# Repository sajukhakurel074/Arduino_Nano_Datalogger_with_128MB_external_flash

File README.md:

# DataLogger

This PCB consist of :
- a pressure sensor -> BMP180
- Acclerometer & Gyroscope -> MPU 6050 
- SD Card Module
- Arduino NANO  
- 12V DC power supply
- 2 layer PCB
- 128MB external Flash with spi

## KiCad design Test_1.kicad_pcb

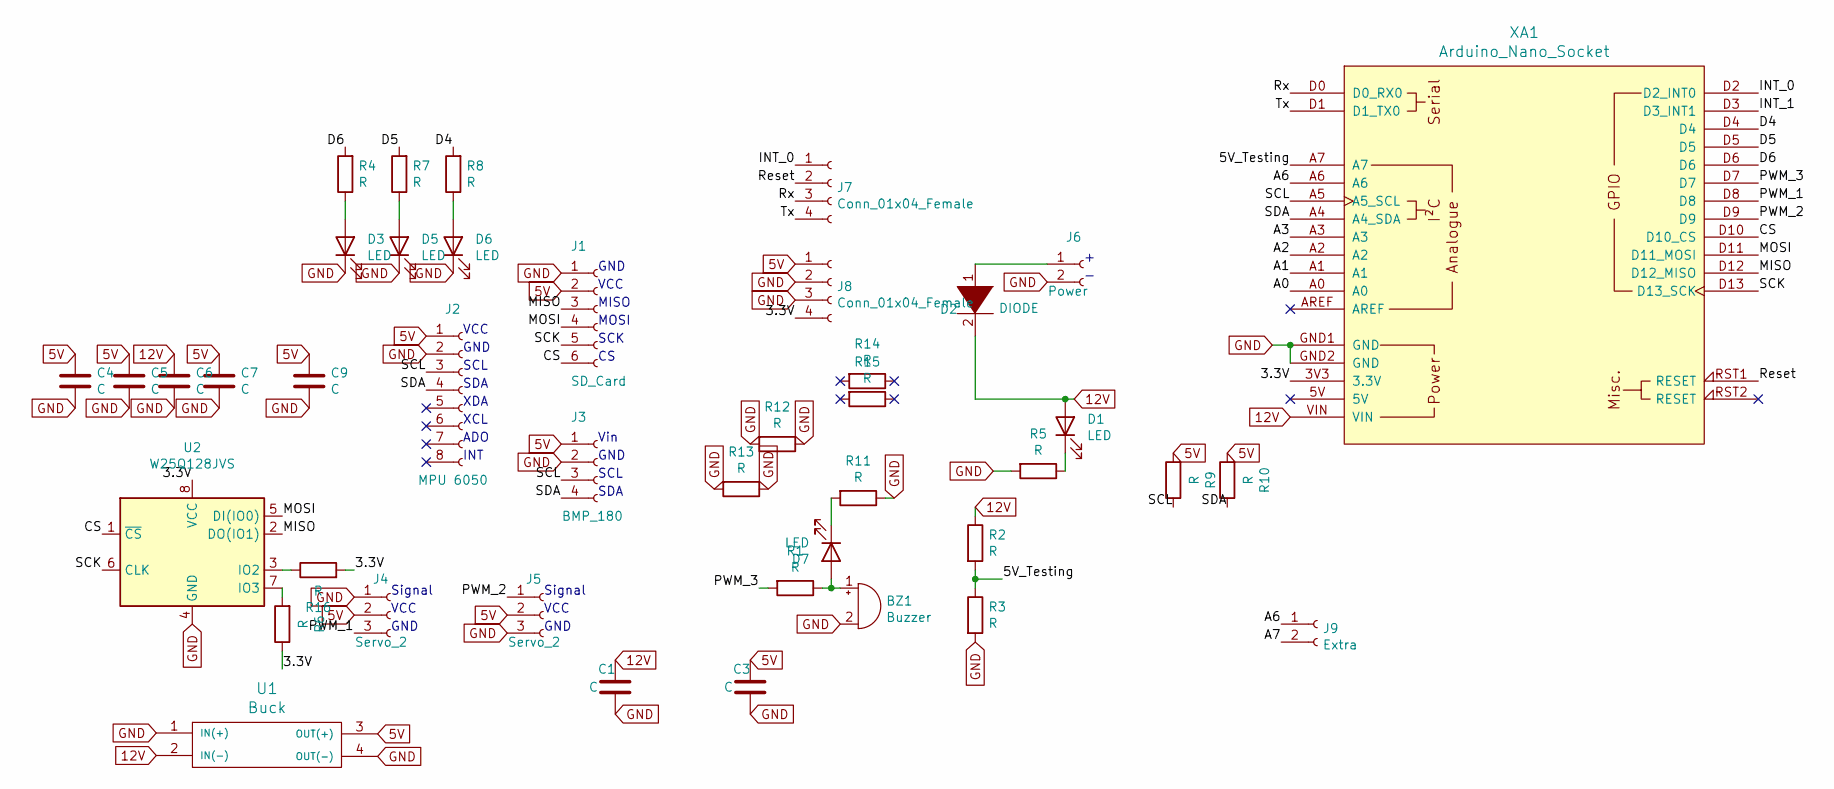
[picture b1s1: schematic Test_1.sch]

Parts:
BZ1: Buzzer; Buzzer_12x9.5RM7.6
C1, C3: C; Capacitor_100uF
C4, C5, C6, C7, C9: C; Capacitor_Disc_Small
D1, D3, D5, D6, D7: LED; LED_D3.0mm
D2: DIODE; Diode_Medium
J1: SD_Card; PinSocket_1x06_P2.54mm_Vertical
J2: MPU 6050; PinSocket_1x08_P2.54mm_Vertical
J3: BMP_180; PinSocket_1x04_P2.54mm_Vertical
J4, J5: Servo_2; Connector_Bornier_3
J6: Power; Solar_Connector
J7, J8: Conn_01x04_Female; PinSocket_1x04_P2.54mm_Vertical
J9: Extra; PinHeader_1x02_P2.54mm_Vertical
R1, R2, R3, R4, R5, R6, R7, R8, R9, R10, R11, R12, R13, R14, R15, R16: R; Resistor_small
U1: Buck; Buck 5A
U2: W25Q128JVS; dip8
XA1: Arduino_Nano_Socket

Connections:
5V: C3.2, C4.1, C5.1, C7.1, C9.1, J1.2, J2.1, J3.1, J4.2, J5.2, J8.1, R9.2, R10.2, U1.3 (OUT(+))
12V: C1.2, C6.1, D1.2 (A), D2.2 (A), R2.1, U1.2 (IN(-)), XA1.VIN
/3.3V: J8.4, R6.1, R16.2, U2.8 (VCC), XA1.3V3 (3.3V)
/5V_Testing: R2.2, R3.1, XA1.A7
/A0: XA1.A0
/A1: XA1.A1
/A2: XA1.A2
/A6: J9.1, XA1.A6
/CS: J1.6, U2.1 (~CS), XA1.D10 (D10_CS)
/D4: R8.2, XA1.D4
/D5: R7.2, XA1.D5
/D6: R4.2, XA1.D6
/INT_0: J7.1, XA1.D2 (D2_INT0)
/INT_1: XA1.D3 (D3_INT1)
/MISO: J1.3, U2.2 (DO(IO1)), XA1.D12 (D12_MISO)
/MOSI: J1.4, U2.5 (DI(IO0)), XA1.D11 (D11_MOSI)
/PWM_1: J4.3, XA1.D8
/PWM_2: J5.1, XA1.D9
/PWM_3: R1.2, XA1.D7
/Reset: J7.2, XA1.RST1 (RESET)
/Rx: J7.3, XA1.D0 (D0_RX0)
/SCK: J1.5, U2.6 (CLK), XA1.D13 (D13_SCK)
/SCL: J2.3, J3.3, R9.1, XA1.A5 (A5_SCL)
/SDA: J2.4, J3.4, R10.1, XA1.A4 (A4_SDA)
/Tx: J7.4, XA1.D1 (D1_TX0)
GND: BZ1.2 (+), C1.1, C3.1, C4.2, C5.2, C6.2, C7.2, C9.2, D3.1 (K), D5.1 (K), D6.1 (K), J1.1, J2.2, J3.2, J4.1, J5.3, J6.2, J8.2, J8.3, R3.2, R5.2, R11.1, R12.1, R12.2, R13.1, R13.2, U1.1 (IN(+)), U1.4 (OUT(-)), U2.4 (GND), XA1.GND1 (GND), XA1.GND2 (GND); also elsewhere on the board
unnamed: BZ1.1 (-), D7.2 (A), R1.1
unnamed: D1.1 (K), R5.1
unnamed: D2.1 (K), J6.1
unnamed: D3.2 (A), R4.1
unnamed: D5.2 (A), R7.1
unnamed: D6.2 (A), R8.1
unnamed: D7.1 (K), R11.2
unnamed: R6.2, U2.7 (IO3)
unnamed: R16.1, U2.3 (IO2)

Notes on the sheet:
GND
VCC
MISO
MOSI
SCK
Signal
VCC
GND
SCL
SDA
XDA
XCL
ADO
INT
Vin

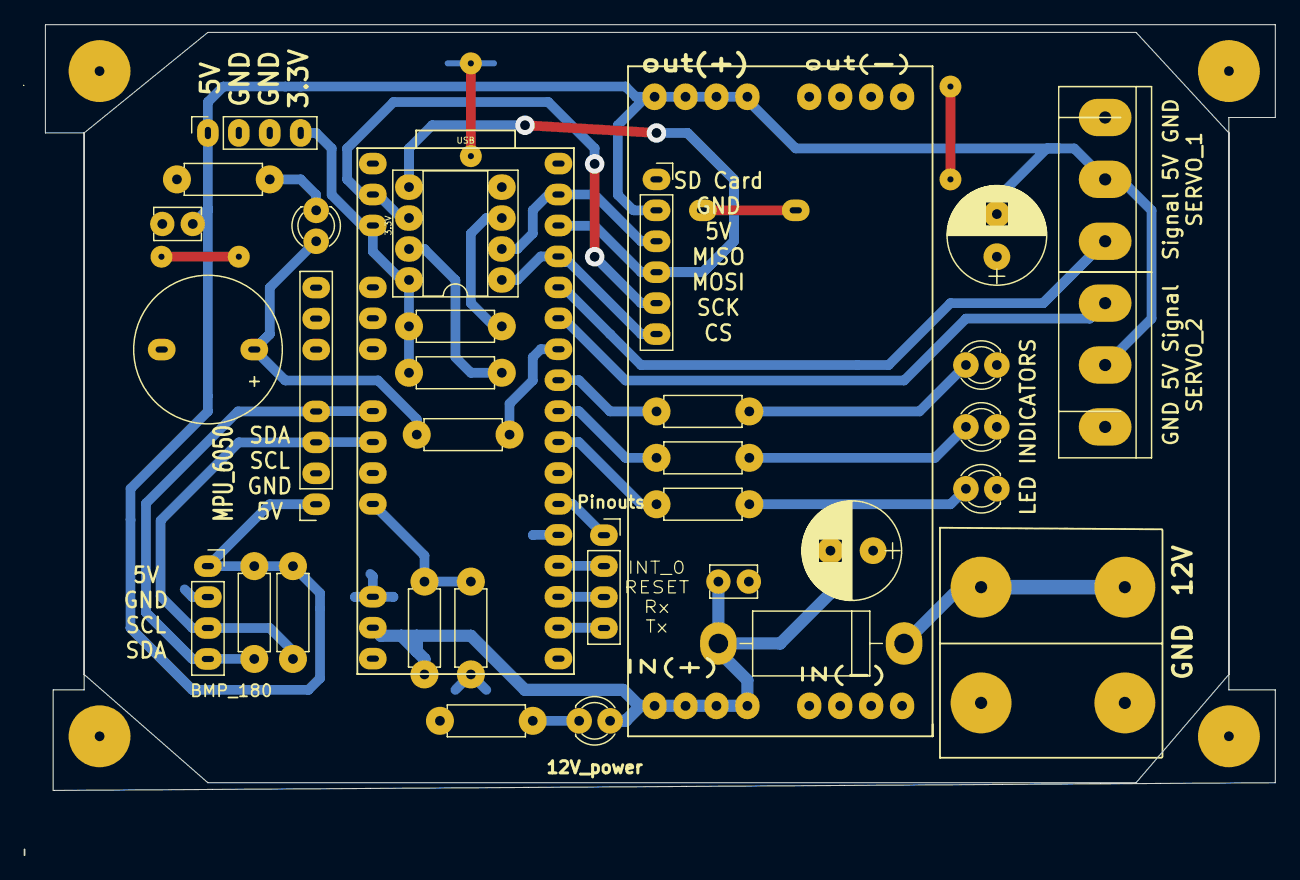
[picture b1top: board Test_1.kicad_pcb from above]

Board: 2 copper layers, 102.7 x 68.2 mm, 40 parts (0 on the bottom side), 30 nets.

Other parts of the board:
R12#2, R12#3: R; Resistor_small

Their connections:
GND: R12#2.1, R12#2.2, R12#3.1, R12#3.2; also elsewhere on the board

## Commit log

2021-08-26 datalogger_circuit_1
2023-04-16 Add Readme File
